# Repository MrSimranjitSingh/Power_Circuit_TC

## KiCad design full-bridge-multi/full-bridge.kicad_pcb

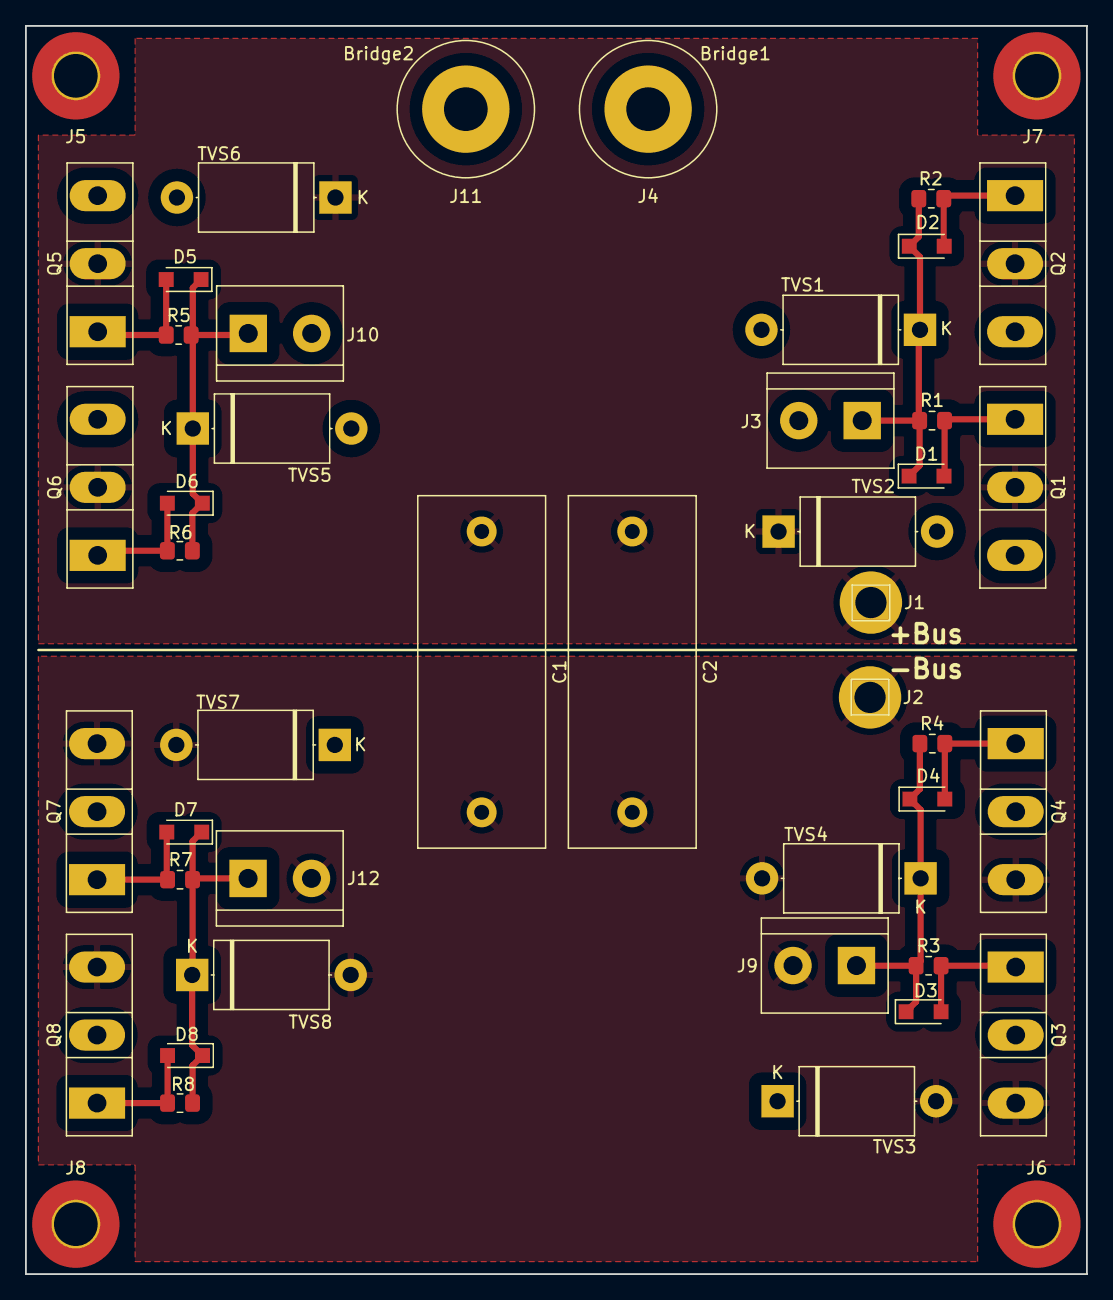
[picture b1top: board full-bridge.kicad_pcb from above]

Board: 2 copper layers, 85.0 x 100.0 mm, 46 parts (0 on the bottom side), 16 nets.

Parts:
C1, C2: 1 uF; C_Rect_L28.0mm_W10.0mm_P22.50mm_MKS4
D1, D2, D3, D4, D5, D6, D7, D8: 1N5819; Nexperia_CFP3_SOD-123W
J1: PosBus; Pin_D1.4mm_L8.5mm_W2.8mm_FlatFork
J2: NegBus; Pin_D1.4mm_L8.5mm_W2.8mm_FlatFork
J3, J9, J10, J12: Screw_Terminal_01x02; TerminalBlock_bornier-2_P5.08mm
J4: Bridge1; Banana_Jack_1Pin
J5, J6, J7, J8: Conn_01x01; MountingHole_3.5mm_Pad_TopBottom
J11: Bridge2; Banana_Jack_1Pin
Q1, Q2, Q3, Q4, Q5, Q6, Q7, Q8: Q_NIGBT_GCE; TO-247-3_Vertical
R1, R2, R3, R5, R6, R7, R8: 10; R_0805_2012Metric_Pad1.20x1.40mm_HandSolder
R4: locked; R_0805_2012Metric_Pad1.20x1.40mm_HandSolder
TVS1, TVS4, TVS5, TVS8: 1.5KE27CA; D_DO-201AE_P12.70mm_Horizontal
TVS2, TVS3, TVS6, TVS7: 1.5KE220CA; D_DO-201AE_P12.70mm_Horizontal

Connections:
GND: C1.2, C2.2, J2.1, J9.2, J12.2, Q3.3 (E), Q4.3 (E), Q7.3 (E), Q8.3 (E), TVS3.2 (A), TVS4.2 (A), TVS7.2 (A), TVS8.2 (A)
unnamed: D1.2 (A), Q1.1 (G), R1.1
unnamed: D1.1 (K), D2.1 (K), J3.1, R1.2, R2.2, TVS1.1 (K)
unnamed: D2.2 (A), Q2.1 (G), R2.1
unnamed: D3.2 (A), Q3.1 (G), R3.1
unnamed: D3.1 (K), D4.1 (K), J9.1, R3.2, R4.2, TVS4.1 (K)
unnamed: D4.2 (A), Q4.1 (G), R4.1
unnamed: D5.2 (A), Q5.1 (G), R5.1
unnamed: D5.1 (K), D6.1 (K), J10.1, R5.2, R6.2, TVS5.1 (K)
unnamed: D6.2 (A), Q6.1 (G), R6.1
unnamed: D7.2 (A), Q7.1 (G), R7.1
unnamed: D7.1 (K), D8.1 (K), J12.1, R7.2, R8.2, TVS8.1 (K)
unnamed: D8.2 (A), Q8.1 (G), R8.1
Primary_1: J3.2, J4.1, Q1.3 (E), Q2.3 (E), Q3.2 (C), Q4.2 (C), TVS1.2 (A), TVS2.2 (A), TVS3.1 (K)
Primary_2: J10.2, J11.1, Q5.3 (E), Q6.3 (E), Q7.2 (C), Q8.2 (C), TVS5.2 (A), TVS6.2 (A), TVS7.1 (K)
VDD: C1.1, C2.1, J1.1, Q1.2 (C), Q2.2 (C), Q5.2 (C), Q6.2 (C), TVS2.1 (K), TVS6.1 (K)
